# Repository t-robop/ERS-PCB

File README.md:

# ERS-PCB

## Description
Atlas，Spicaプロジェクトでのロボット用の基板．

## Requirements

### Fritzing

Fritzing Version 0.9.3 or later

### KiCad

KiCad 5.0.x or later

### Eagle

Eagle 9.x or later

### Author
multiverse2011, nishimura

### License
MIT

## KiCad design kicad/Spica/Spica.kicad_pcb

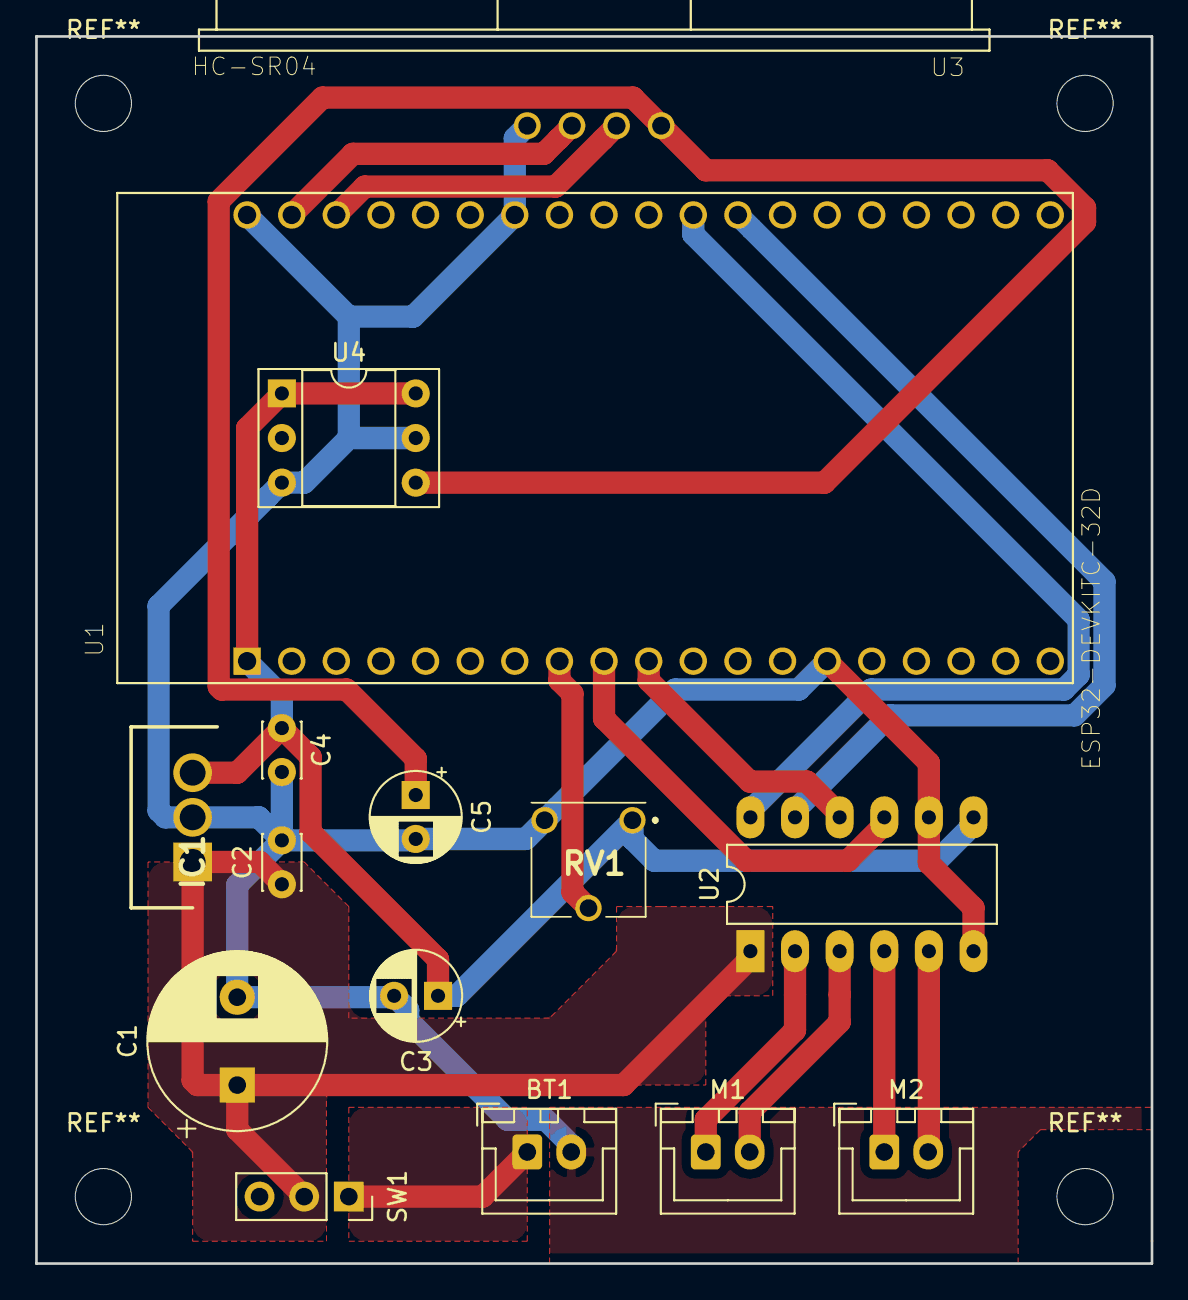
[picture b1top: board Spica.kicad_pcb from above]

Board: 2 copper layers, 63.5 x 69.8 mm, 15 parts (0 on the bottom side), 16 nets.

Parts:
BT1: Battery_Cell; JST_XH_B02B-XH-A_1x02_P2.50mm_Vertical
C1: 1000μ; CP_Radial_D10.0mm_P5.00mm
C2, C4: 0.1μ; C_Disc_D3.0mm_W2.0mm_P2.50mm
C3: 100μ; CP_Radial_D5.0mm_P2.50mm
C5: 10μ; CP_Radial_D5.0mm_P2.50mm
IC1: TA48033S; TO254P490X1000X2090-3P
M1, M2: Motor_DC; JST_XH_B02B-XH-A_1x02_P2.50mm_Vertical
RV1: 10k; TSR065103R
SW1: SW_SPDT; PinSocket_1x03_P2.54mm_Vertical
U1: ESP32-DEVKITC-32D; MODULE_ESP32-DEVKITC-32D
U2: DRV8835-akizuki; DIP-12_W7.62mm_LongPads
U3: HC-SR04; XCVR_HC-SR04
U4: AE-XCL102D503CR-G; DIP-6_W7.62mm_Socket

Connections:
3.3V: C3.1, C4.1, IC1.3, RV1.1, U1.1, U2.7, U4.1, U4.6
5V: C5.1, U3.1, U4.4
GND: BT1.2, C1.2, C2.2, C3.2, C4.2, C5.2, IC1.2, RV1.3, U1.14, U1.20, U1.26, U2.6, U2.8, U3.4, U4.3, U4.5
IO16: U1.31, U2.11
IO17: U1.30, U2.12
IO22: U1.22, U3.2
IO23: U1.21, U3.3
IO25: U1.9, U2.9
IO26: U1.10, U2.10
unnamed: BT1.1, SW1.1
unnamed: M1.1, U2.2
unnamed: M1.2, U2.3
unnamed: M2.1, U2.4
unnamed: M2.2, U2.5
unnamed: RV1.2, U1.8
VCC: C1.1, C2.1, IC1.1, SW1.2, U2.1

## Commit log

2017-05-31 Create partsList
2017-05-31 Rename partsList to partsList.txt
2017-07-04 Type-Xの追加、スイッチの向きの修正
2017-10-02 Finished product edition
2017-10-18 resize&reallocation🎉
2017-10-18 Production version🎉
2017-10-31 謎のブリッジを削除
2017-10-31 旧Type-Xの削除
2018-08-15 spicaを追加
2018-08-16 半固定抵抗を追加
2018-08-16 PCB配線完了🎉
2018-08-16 Rename&整理
2018-10-04 一旦ブリッジしてるところを修正
2018-10-05 60mmx60mmに押し込んだ
2018-10-06 レイアウトの整理
2018-10-06 パーツラベルを整理
2018-10-07 Productionの1歩手前
2018-11-03 Add KiCad files
2018-11-05 Add some Akizuki parts
2018-11-05 Finish rooting
2018-11-07 Add surface GND
2018-11-07 ベタパターンを追加
2018-11-07 細かな修正
2018-11-07 Add eagle files
